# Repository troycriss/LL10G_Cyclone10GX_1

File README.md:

LL10G_Cyclone10GX_1

Test of 10 Gb ethernet output from Cyclone 10 GX dev kit

All switches up (OFF, 1) except S3_2 (and S2_1)
For FMC JTAG not in use, set S5_1 to 0

Quartus Pro 18.1

Program with .sof (via .cdf to open programmer)<br>
Runs for unlimited time, but can't program permanently<br>
See heartbeat LED<br>
Reset Arduino with soft_i2c_cyclone10gx to program SFP outputs (level shifted to 1.8 V)<br>
See red, then green, SFP LEDs<br>
Open system console<br>

 cd hwtesting\\system_console
 
 source main.tcl
 
 SEND 0 10G 80
 
 SENDAGAIN

Set reset pulse duration with (ex: 8) :
 PULSES_pos1dur <duration>

Set write pulse duration with (ex: 7) :
 PULSES_pos2dur <duration>

Set read pulse duration with (ex: 30) :
 PULSES_pos3dur <duration>

https://en.wikipedia.org/wiki/Ethernet_frame <br>
https://en.wikipedia.org/wiki/Internet_Protocol_version_4 <br>
https://en.wikipedia.org/wiki/User_Datagram_Protocol <br>

mac64b_clk; // 156.25 MHz via pll<br>
6.4ns per tick<br>

C10GX kit download: https://www.dropbox.com/s/qehok7muoahcpib/cyclone-10-gx-kit-collateral.zip?dl=0 <br>
  Board test system: https://www.dropbox.com/sh/13s1js1465clt0y/AADcKpqSJ-fH7NIdkqhGLnxYa?dl=0 <br>
  Factory recovery: https://www.dropbox.com/sh/fvxx9ef50a99x4v/AAATVMVC8e21aiI6xPSL01WCa?dl=0 <br>

Simulation of amps: 
https://tinyurl.com/297t5xo8

Simulation of pulse generators:
https://tinyurl.com/27l9ev2u

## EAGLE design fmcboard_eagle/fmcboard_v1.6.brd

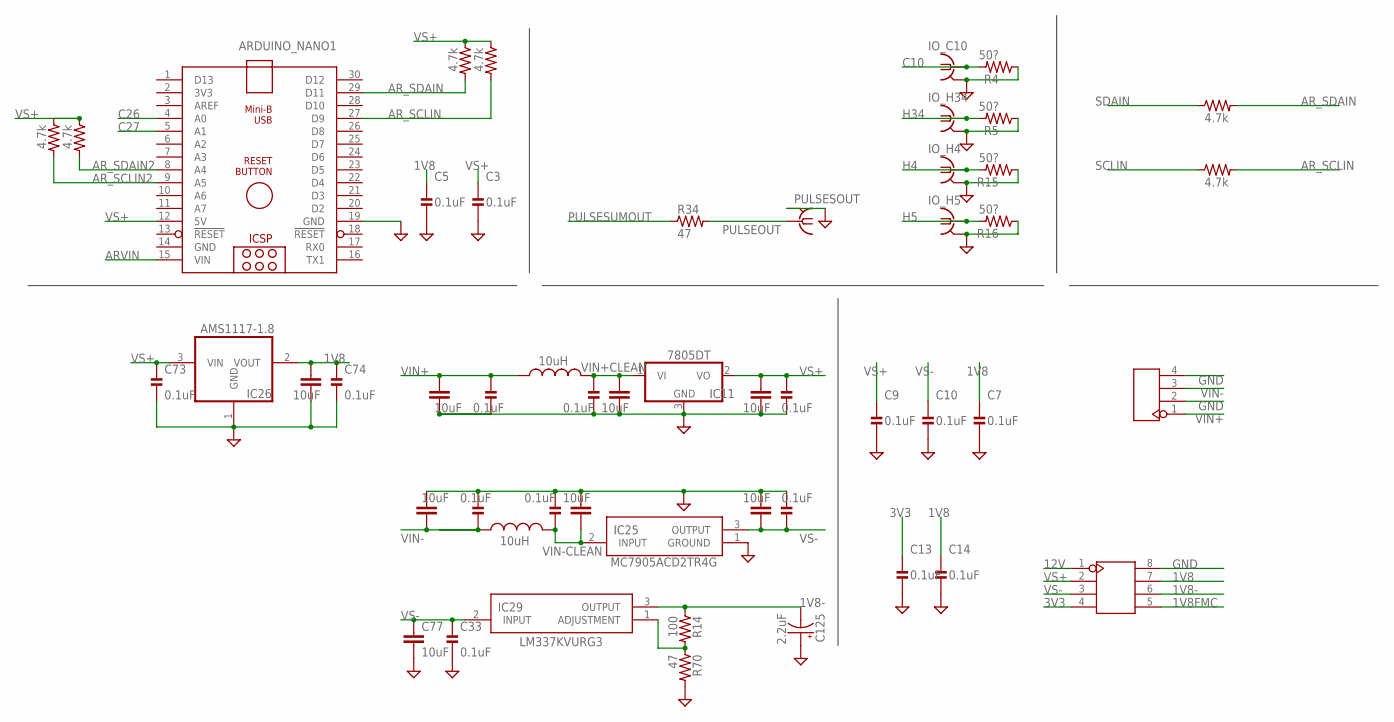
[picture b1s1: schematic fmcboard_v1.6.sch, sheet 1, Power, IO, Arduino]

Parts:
ARDUINO_NANO1: 1; ARDUINO_NANO
C1, C34, C38, C39, C41, C77, C110, C111: 10uF; C0805
C3, C5, C7, C9, C10, C13, C14, C33, C42, C43, C44, C45, C46, C47, C73, C74: 0.1uF; 0402_CAP
C125: 2.2uF; EIA3216; JLC_ROTATION 180
IC11: 7805DT; TO252
IC25: MC7905ACD2TR4G
IC26: AMS1117-1.8; SOT223; JLC_ROTATION 270
IC29: LM337KVURG3
IO_C10: BU-SMB-V
IO_H4, IO_H5, IO_H34: BU-SMB-V
J1: 4p-2.54; H4-2.54
J3: 2X4P-2.54; H2X4-2.54
L1, L2: 10uH; 1210
PULSESOUT: BU-SMB-V
R4, R5, R15, R16: 50?; 0402_RES
R14: 100; 0402_RES
R34, R70: 47; 0402_RES
R48, R49, R50, R51, R87, R90: 4.7k; 0402_RES

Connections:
1V8: C5.1, C7.1, C14.1, C34.1, C74.1, IC26.2 (VOUT), J3.7; also elsewhere on the board
1V8-: C125.C (-), IC29.3 (OUTPUT), J3.6, R14.1; also elsewhere on the board
1V8FMC: J3.5; also elsewhere on the board
3V3: C13.1, J3.4; also elsewhere on the board
12V: J3.1; also elsewhere on the board
ARVIN: ARDUINO_NANO1.15 (VIN)
AR_SCLIN: ARDUINO_NANO1.27 (D9), R51.2, R90.2
AR_SCLIN2: ARDUINO_NANO1.9 (A5), R49.2; also elsewhere on the board
AR_SDAIN: ARDUINO_NANO1.29 (D11), R50.2, R87.2
AR_SDAIN2: ARDUINO_NANO1.8 (A4), R48.2; also elsewhere on the board
C10: IO_C10.1, R4.2; also elsewhere on the board
C26: ARDUINO_NANO1.4 (A0); also elsewhere on the board
C27: ARDUINO_NANO1.5 (A1); also elsewhere on the board
GND: ARDUINO_NANO1.14 (GND), ARDUINO_NANO1.19 (GND), C1.2, C3.2, C5.2, C7.2, C9.2, C10.2, C13.2, C14.2, C33.2, C34.2, C38.2, C39.1, C41.1, C42.2, C43.2, C44.1, C45.1, C46.1, C47.2, C73.2, C74.2, C77.2, C110.2, C111.1, C125.A (+), IC11.3 (GND), IC25.1 (GROUND), IC26.1 (GND), IO_C10.2, IO_C10.3 (2), IO_C10.4 (2), IO_C10.5 (2), IO_H4.2, IO_H4.3 (2), IO_H4.4 (2), IO_H4.5 (2), IO_H5.2, IO_H5.3 (2), IO_H5.4 (2), IO_H5.5 (2), IO_H34.2, IO_H34.3 (2), IO_H34.4 (2), IO_H34.5 (2), J1.2, J1.4, J3.8, PULSESOUT.2, PULSESOUT.3 (2), PULSESOUT.4 (2), PULSESOUT.5 (2), R4.1, R5.1, R15.1, R16.1, R70.2; also elsewhere on the board
H4: IO_H4.1, R15.2; also elsewhere on the board
H5: IO_H5.1, R16.2; also elsewhere on the board
H34: IO_H34.1, R5.2; also elsewhere on the board
unnamed: IC29.1 (ADJUSTMENT), R14.2, R70.1
PULSEOUT: PULSESOUT.1, R34.2; also elsewhere on the board
PULSESUMOUT: R34.1; also elsewhere on the board
SCLIN: R90.1; also elsewhere on the board
SDAIN: R87.1; also elsewhere on the board
VIN+: C1.1, C42.1, J1.1, L1.1; also elsewhere on the board
VIN+CLEAN: C43.1, C110.1, IC11.1 (VI), L1.2
VIN-: C41.2, C44.2, J1.3, L2.1; also elsewhere on the board
VIN-CLEAN: C45.2, C111.2, IC25.2 (INPUT), L2.2
VS+: ARDUINO_NANO1.12 (5V), C3.1, C9.1, C38.1, C47.1, C73.1, IC11.2 (VO), IC26.3 (VIN), J3.2, R48.1, R49.1, R50.1, R51.1; also elsewhere on the board
VS-: C10.1, C33.1, C39.2, C46.2, C77.1, IC25.3 (OUTPUT), IC29.2 (INPUT), J3.3; also elsewhere on the board

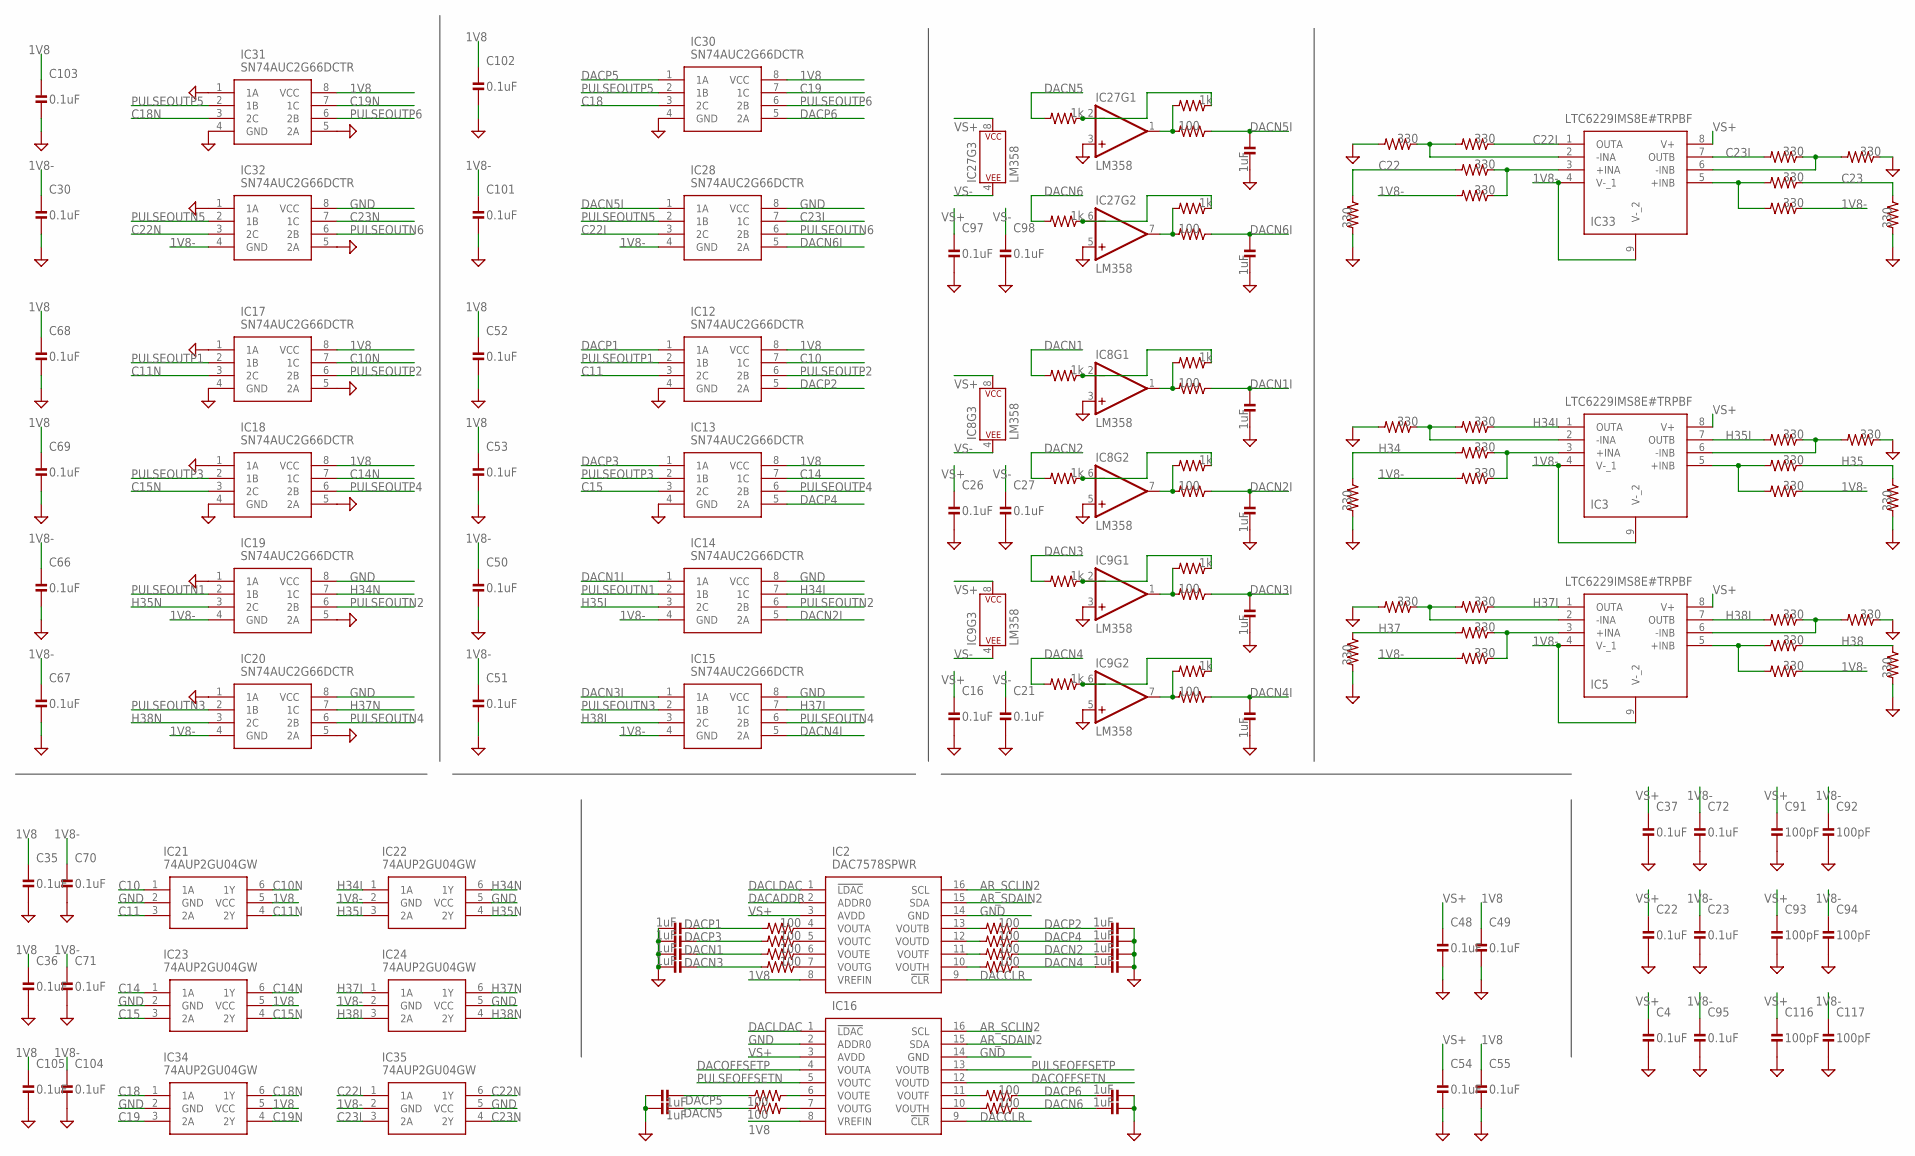
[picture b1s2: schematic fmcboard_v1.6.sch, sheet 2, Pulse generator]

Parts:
C4, C16, C21, C22, C23, C26, C27, C30, C35, C36, C37, C48, C49, C50, C51, C52, C53, C54, C55, C66, C67, C68, C69, C70, C71, C72, C95, C97, C98, C101, C102, C103, C104, C105: 0.1uF; 0402_CAP
C17, C18, C19, C20, C31, C56, C57, C58, C59, C60, C61, C62, C63, C89, C90, C96, C99, C100: 1uF; 0402_CAP
C91, C92, C93, C94, C116, C117: 100pF; 0402_CAP
IC2, IC16: DAC7578SPWR; SOP65P640X120-16N
IC3, IC5, IC33: LTC6229IMS8E#TRPBF; SOP65P490X110-9N
IC8, IC9, IC27: LM358; SO08
IC12, IC13, IC14, IC15, IC17, IC18, IC19, IC20, IC28, IC30, IC31, IC32: SN74AUC2G66DCTR; SOP65P400X130-8N
IC21, IC22, IC23, IC24, IC34, IC35: 74AUP2GU04GW; SOT65P210X110-6N
R21, R22, R23, R24, R27, R28, R29, R30, R37, R39, R41, R43, R44, R45, R46, R52, R80, R81, R82, R83, R91, R102, R103, R104, R105, R106, R107, R108, R109, R110: 330; 0402_RES
R47, R53, R54, R55, R56, R57, R58, R59, R74, R75, R76, R77, R92, R93, R94, R95, R100, R101: 100; 0402_RES
R62, R63, R64, R65, R66, R67, R68, R69, R96, R97, R98, R99: 1k; 0402_RES

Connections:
1V8: C35.1, C36.1, C49.1, C52.1, C53.1, C55.1, C68.1, C69.1, C102.1, C103.1, C105.1, IC2.8 (VREFIN), IC12.8 (VCC), IC13.8 (VCC), IC16.8 (VREFIN), IC17.8 (VCC), IC18.8 (VCC), IC21.5 (VCC), IC23.5 (VCC), IC30.8 (VCC), IC31.8 (VCC), IC34.5 (VCC); also elsewhere on the board
1V8-: C23.1, C30.1, C50.1, C51.1, C66.1, C67.1, C70.1, C71.1, C72.1, C92.1, C94.1, C95.1, C101.1, C104.1, C117.1, IC3.4 (V-_1), IC3.9 (V-_2), IC5.4 (V-_1), IC5.9 (V-_2), IC14.4 (GND), IC15.4 (GND), IC19.4 (GND), IC20.4 (GND), IC22.2 (GND), IC24.2 (GND), IC28.4 (GND), IC32.4 (GND), IC33.4 (V-_1), IC33.9 (V-_2), IC35.2 (GND), R22.2, R28.1, R39.2, R45.1, R102.2, R106.1; also elsewhere on the board
AR_SCLIN2: IC2.16 (SCL), IC16.16 (SCL); also elsewhere on the board
AR_SDAIN2: IC2.15 (SDA), IC16.15 (SDA); also elsewhere on the board
C10: IC12.7 (1C), IC21.1 (1A); also elsewhere on the board
C10N: IC17.7 (1C), IC21.6 (1Y)
C11: IC12.3 (2C), IC21.3 (2A); also elsewhere on the board
C11N: IC17.3 (2C), IC21.4 (2Y)
C14: IC13.7 (1C), IC23.1 (1A); also elsewhere on the board
C14N: IC18.7 (1C), IC23.6 (1Y)
C15: IC13.3 (2C), IC23.3 (2A); also elsewhere on the board
C15N: IC18.3 (2C), IC23.4 (2Y)
C18: IC30.3 (2C), IC34.1 (1A); also elsewhere on the board
C18N: IC31.3 (2C), IC34.6 (1Y)
C19: IC30.7 (1C), IC34.3 (2A); also elsewhere on the board
C19N: IC31.7 (1C), IC34.4 (2Y)
C22: R91.2, R109.1; also elsewhere on the board
C22I: IC28.3 (2C), IC33.1 (OUTA), IC35.1 (1A), R103.1
C22N: IC32.3 (2C), IC35.6 (1Y)
C23: R105.1, R110.1; also elsewhere on the board
C23I: IC28.7 (1C), IC33.7 (OUTB), IC35.3 (2A), R107.2
C23N: IC32.7 (1C), IC35.4 (2Y)
DACADDR: IC2.2 (ADDR0)
DACCLR: IC2.9 (!CLR), IC16.9 (!CLR)
DACLDAC: IC2.1 (!LDAC), IC16.1 (!LDAC)
DACN1: C57.2, R54.2, R64.2
DACN1I: C17.2, IC14.1 (1A), R74.1
DACN2: C61.1, R58.1, R65.2
DACN2I: C18.2, IC14.5 (2A), R75.1
DACN3: C56.2, R55.2, R68.2
DACN3I: C19.2, IC15.1 (1A), R76.1
DACN4: C60.1, R59.1, R69.2
DACN4I: C20.2, IC15.5 (2A), R77.1
DACN5: C96.1, R95.1, R98.2
DACN5I: C99.2, IC28.1 (1A), R100.1
DACN6: C89.1, R93.1, R99.2
DACN6I: C100.2, IC28.5 (2A), R101.1
DACOFFSETN: IC16.12 (VOUTD); also elsewhere on the board
DACOFFSETP: IC16.4 (VOUTA); also elsewhere on the board
DACP1: C59.2, IC12.1 (1A), R47.2
DACP2: C63.1, IC12.5 (2A), R56.1
DACP3: C58.2, IC13.1 (1A), R53.2
DACP4: C62.1, IC13.5 (2A), R57.1
DACP5: C90.1, IC30.1 (1A), R94.1
DACP6: C31.1, IC30.5 (2A), R92.1
GND: C4.2, C16.2, C17.1, C18.1, C19.1, C20.1, C21.2, C22.2, C23.2, C26.2, C27.2, C30.2, C31.2, C35.2, C36.2, C37.2, C48.2, C49.2, C50.2, C51.2, C52.2, C53.2, C54.2, C55.2, C56.1, C57.1, C58.1, C59.1, C60.2, C61.2, C62.2, C63.2, C66.2, C67.2, C68.2, C69.2, C70.2, C71.2, C72.2, C89.2, C90.2, C91.2, C92.2, C93.2, C94.2, C95.2, C96.2, C97.2, C98.2, C99.1, C100.1, C101.2, C102.2, C103.2, C104.2, C105.2, C116.2, C117.2, IC2.14 (GND), IC8.3 (+IN), IC8.5 (+IN), IC9.3 (+IN), IC9.5 (+IN), IC12.4 (GND), IC13.4 (GND), IC14.8 (VCC), IC15.8 (VCC), IC16.2 (ADDR0), IC16.14 (GND), IC17.1 (1A), IC17.4 (GND), IC17.5 (2A), IC18.1 (1A), IC18.4 (GND), IC18.5 (2A), IC19.1 (1A), IC19.5 (2A), IC19.8 (VCC), IC20.1 (1A), IC20.5 (2A), IC20.8 (VCC), IC21.2 (GND), IC22.5 (VCC), IC23.2 (GND), IC24.5 (VCC), IC27.3 (+IN), IC27.5 (+IN), IC28.8 (VCC), IC30.4 (GND), IC31.1 (1A), IC31.4 (GND), IC31.5 (2A), IC32.1 (1A), IC32.5 (2A), IC32.8 (VCC), IC34.2 (GND), IC35.5 (VCC), R24.2, R30.1, R43.2, R52.1, R80.2, R81.2, R82.2, R83.2, R104.2, R108.1, R109.2, R110.2; also elsewhere on the board
H34: R21.2, R80.1; also elsewhere on the board
H34I: IC3.1 (OUTA), IC14.7 (1C), IC22.1 (1A), R23.1
H34N: IC19.7 (1C), IC22.6 (1Y)
H35: R27.1, R81.1; also elsewhere on the board
H35I: IC3.7 (OUTB), IC14.3 (2C), IC22.3 (2A), R29.2
H35N: IC19.3 (2C), IC22.4 (2Y)
H37: R37.2, R83.1; also elsewhere on the board
H37I: IC5.1 (OUTA), IC15.7 (1C), IC24.1 (1A), R41.1
H37N: IC20.7 (1C), IC24.6 (1Y)
H38: R44.1, R82.1; also elsewhere on the board
H38I: IC5.7 (OUTB), IC15.3 (2C), IC24.3 (2A), R46.2
H38N: IC20.3 (2C), IC24.4 (2Y)
unnamed: IC33.2 (-INA), R103.2, R104.1
unnamed: IC3.6 (-INB), R29.1, R30.2
unnamed: IC3.5 (+INB), R27.2, R28.2
unnamed: IC5.2 (-INA), R41.2, R43.1
unnamed: IC3.3 (+INA), R21.1, R22.1
unnamed: IC5.6 (-INB), R46.1, R52.2
unnamed: IC3.2 (-INA), R23.2, R24.1
unnamed: IC5.3 (+INA), R37.1, R39.1
unnamed: IC5.5 (+INB), R44.2, R45.2
unnamed: IC8.7 (OUT), R62.2, R75.2
unnamed: IC8.1 (OUT), R63.2, R74.2
unnamed: IC16.11 (VOUTF), R92.2
unnamed: IC8.2 (-IN), R63.1, R64.1
unnamed: IC8.6 (-IN), R62.1, R65.1
unnamed: IC2.13 (VOUTB), R56.2
unnamed: IC2.4 (VOUTA), R47.1
unnamed: IC2.5 (VOUTC), R53.1
unnamed: IC2.6 (VOUTE), R54.1
unnamed: IC2.7 (VOUTG), R55.1
unnamed: IC2.12 (VOUTD), R57.2
unnamed: IC2.11 (VOUTF), R58.2
unnamed: IC2.10 (VOUTH), R59.2
unnamed: IC9.7 (OUT), R66.2, R77.2
unnamed: IC9.1 (OUT), R67.2, R76.2
unnamed: IC9.2 (-IN), R67.1, R68.1
unnamed: IC9.6 (-IN), R66.1, R69.1
unnamed: IC16.10 (VOUTH), R93.2
unnamed: IC16.6 (VOUTE), R94.2
unnamed: IC16.7 (VOUTG), R95.2
unnamed: IC27.7 (OUT), R96.2, R101.2
unnamed: IC27.1 (OUT), R97.2, R100.2
unnamed: IC27.2 (-IN), R97.1, R98.1
unnamed: IC27.6 (-IN), R96.1, R99.1
unnamed: IC33.6 (-INB), R107.1, R108.2
unnamed: IC33.3 (+INA), R91.1, R102.1
unnamed: IC33.5 (+INB), R105.2, R106.2
PULSEOFFSETN: IC16.5 (VOUTC); also elsewhere on the board
PULSEOFFSETP: IC16.13 (VOUTB); also elsewhere on the board
PULSEOUTN1: IC14.2 (1B), IC19.2 (1B); also elsewhere on the board
PULSEOUTN2: IC14.6 (2B), IC19.6 (2B); also elsewhere on the board
PULSEOUTN3: IC15.2 (1B), IC20.2 (1B); also elsewhere on the board
PULSEOUTN4: IC15.6 (2B), IC20.6 (2B); also elsewhere on the board
PULSEOUTN5: IC28.2 (1B), IC32.2 (1B); also elsewhere on the board
PULSEOUTN6: IC28.6 (2B), IC32.6 (2B); also elsewhere on the board
PULSEOUTP1: IC12.2 (1B), IC17.2 (1B); also elsewhere on the board
PULSEOUTP2: IC12.6 (2B), IC17.6 (2B); also elsewhere on the board
PULSEOUTP3: IC13.2 (1B), IC18.2 (1B); also elsewhere on the board
PULSEOUTP4: IC13.6 (2B), IC18.6 (2B); also elsewhere on the board
PULSEOUTP5: IC30.2 (1B), IC31.2 (1B); also elsewhere on the board
PULSEOUTP6: IC30.6 (2B), IC31.6 (2B); also elsewhere on the board
VS+: C4.1, C16.1, C22.1, C26.1, C37.1, C48.1, C54.1, C91.1, C93.1, C97.1, C116.1, IC2.3 (AVDD), IC3.8 (V+), IC5.8 (V+), IC8.8 (P$V+), IC9.8 (P$V+), IC16.3 (AVDD), IC27.8 (P$V+), IC33.8 (V+); also elsewhere on the board
VS-: C21.1, C27.1, C98.1, IC8.4 (P$V-), IC9.4 (P$V-), IC27.4 (P$V-); also elsewhere on the board

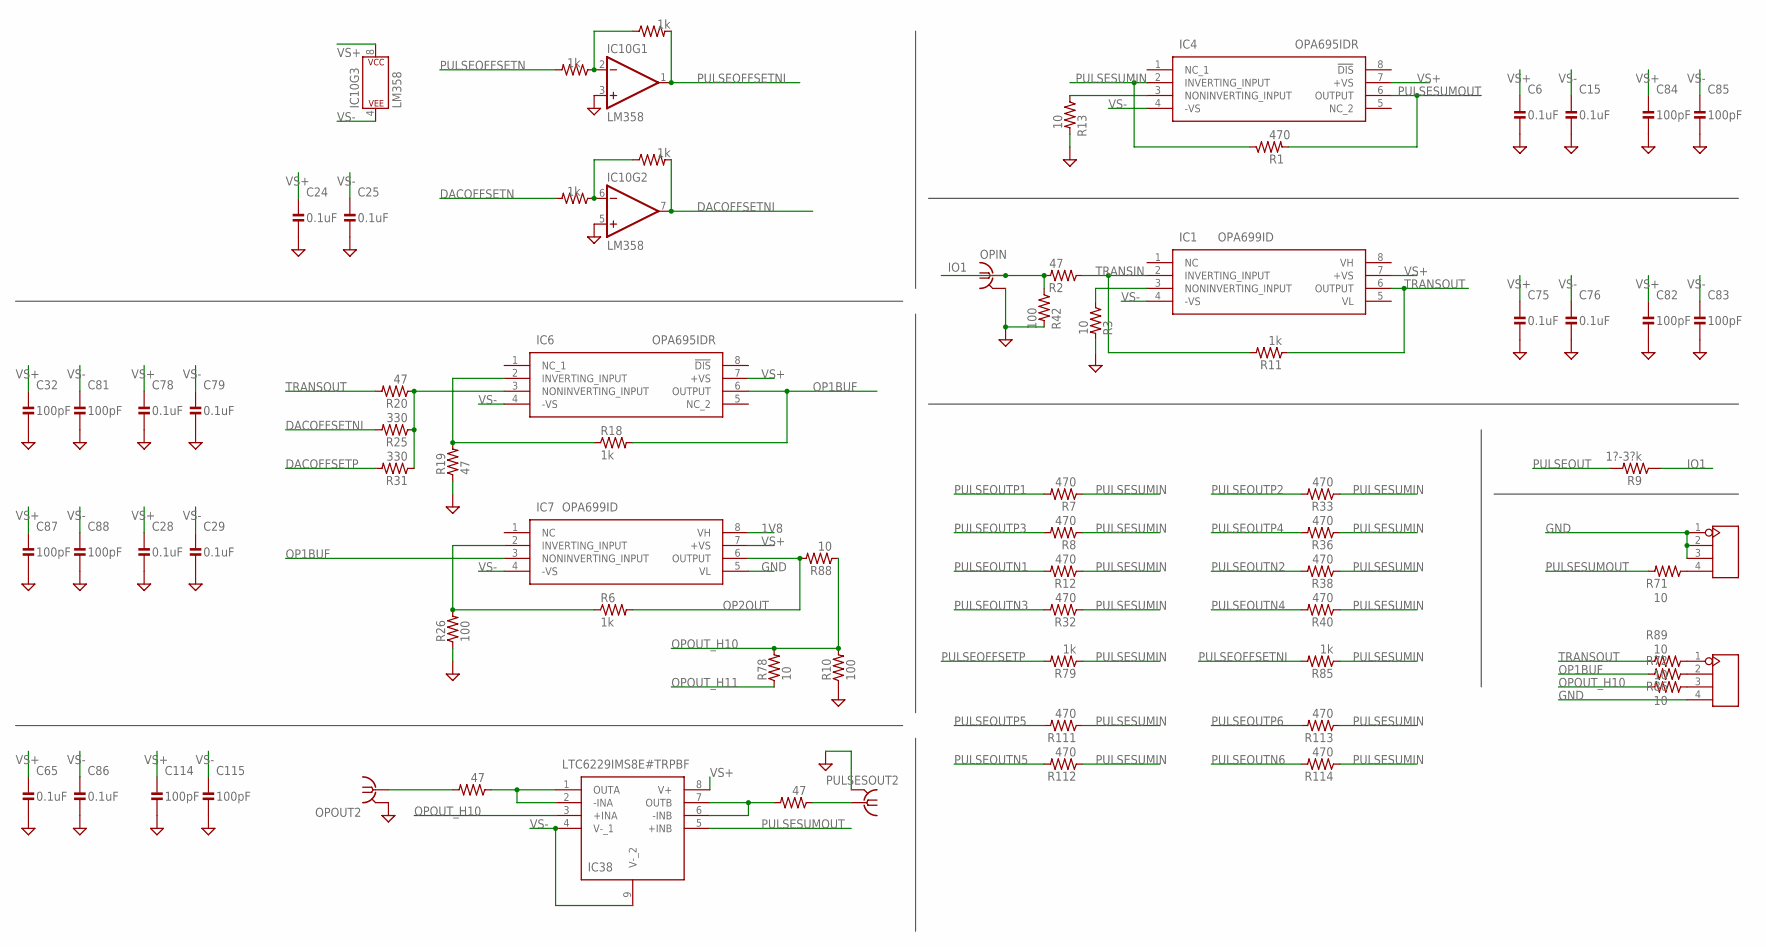
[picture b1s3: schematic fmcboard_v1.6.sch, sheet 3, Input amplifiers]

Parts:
C6, C15, C24, C25, C28, C29, C65, C75, C76, C78, C79, C86: 0.1uF; 0402_CAP
C32, C81, C82, C83, C84, C85, C87, C88, C114, C115: 100pF; 0402_CAP
IC1, IC7: OPA699ID; SOIC127P600X175-8N
IC4, IC6: OPA695IDR; SOIC127P600X175-8N
IC10: LM358; SO08
IC38: LTC6229IMS8E#TRPBF; SOP65P490X110-9N
J5, J13: 4p-2.54; H4-2.54
OPIN: BU-SMB-V
OPOUT2: BU-SMB-V
PULSESOUT2: BU-SMB-V
R1, R7, R8, R12, R32, R33, R36, R38, R40, R111, R112, R113, R114: 470; 0402_RES
R2, R19, R20, R119, R120: 47; 0402_RES
R3, R13, R71, R72, R78, R86, R88, R89: 10; 0402_RES
R6, R11, R17, R18, R35, R61, R79, R85, R115: 1k; 0402_RES
R9: 1?-3?k; R0805
R10, R26, R42: 100; 0402_RES
R25, R31: 330; 0402_RES

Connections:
1V8: IC7.8 (VH); also elsewhere on the board
DACOFFSETN: R17.2; also elsewhere on the board
DACOFFSETNI: IC10.7 (OUT), R25.2, R115.2
DACOFFSETP: R31.2; also elsewhere on the board
GND: C6.2, C15.2, C24.2, C25.2, C28.2, C29.2, C32.2, C65.2, C75.2, C76.2, C78.2, C79.2, C81.2, C82.2, C83.2, C84.2, C85.2, C86.2, C87.2, C88.2, C114.2, C115.2, IC7.5 (VL), IC10.3 (+IN), IC10.5 (+IN), J5.4, J13.1, J13.2, J13.3, OPIN.2, OPIN.3 (2), OPIN.4 (2), OPIN.5 (2), OPOUT2.2, OPOUT2.3 (2), OPOUT2.4 (2), OPOUT2.5 (2), PULSESOUT2.2, PULSESOUT2.3 (2), PULSESOUT2.4 (2), PULSESOUT2.5 (2), R3.2, R10.1, R13.2, R19.1, R26.1, R42.2; also elsewhere on the board
IO1: OPIN.1, R2.2, R9.1, R42.1
unnamed: IC10.6 (-IN), R17.1, R115.1
unnamed: IC1.3 (NONINVERTING_INPUT), R3.1
unnamed: IC4.3 (NONINVERTING_INPUT), R13.1
unnamed: IC6.2 (INVERTING_INPUT), R18.1, R19.2
unnamed: IC6.3 (NONINVERTING_INPUT), R20.1, R25.1, R31.1
unnamed: IC7.2 (INVERTING_INPUT), R6.1, R26.2
unnamed: IC38.1 (OUTA), IC38.2 (-INA), R119.1
unnamed: J5.2, R72.1
unnamed: IC10.2 (-IN), R35.1, R61.1
unnamed: PULSESOUT2.1, R120.1
unnamed: J5.3, R86.1
unnamed: J5.1, R89.1
unnamed: OPOUT2.1, R119.2
unnamed: J13.4, R71.1
unnamed: IC38.6 (-INB), IC38.7 (OUTB), R120.2
OP1BUF: IC6.6 (OUTPUT), IC7.3 (NONINVERTING_INPUT), R18.2, R72.2
OP2OUT: IC7.6 (OUTPUT), R6.2, R88.2
OPOUT_H10: IC38.3 (+INA), R10.2, R78.2, R86.2, R88.1; also elsewhere on the board
OPOUT_H11: R78.1; also elsewhere on the board
PULSEOFFSETN: R61.2; also elsewhere on the board
PULSEOFFSETNI: IC10.1 (OUT), R35.2, R85.2
PULSEOFFSETP: R79.2; also elsewhere on the board
PULSEOUT: R9.2; also elsewhere on the board
PULSEOUTN1: R12.2; also elsewhere on the board
PULSEOUTN2: R38.2; also elsewhere on the board
PULSEOUTN3: R32.2; also elsewhere on the board
PULSEOUTN4: R40.2; also elsewhere on the board
PULSEOUTN5: R112.2; also elsewhere on the board
PULSEOUTN6: R114.2; also elsewhere on the board
PULSEOUTP1: R7.2; also elsewhere on the board
PULSEOUTP2: R33.2; also elsewhere on the board
PULSEOUTP3: R8.2; also elsewhere on the board
PULSEOUTP4: R36.2; also elsewhere on the board
PULSEOUTP5: R111.2; also elsewhere on the board
PULSEOUTP6: R113.2; also elsewhere on the board
PULSESUMIN: IC4.2 (INVERTING_INPUT), R1.1, R7.1, R8.1, R12.1, R32.1, R33.1, R36.1, R38.1, R40.1, R79.1, R85.1, R111.1, R112.1, R113.1, R114.1
PULSESUMOUT: IC4.6 (OUTPUT), IC38.5 (+INB), R1.2, R71.2; also elsewhere on the board
TRANSIN: IC1.2 (INVERTING_INPUT), R2.1, R11.2
TRANSOUT: IC1.6 (OUTPUT), R11.1, R20.2, R89.2
VS+: C6.1, C24.1, C28.1, C32.1, C65.1, C75.1, C78.1, C82.1, C84.1, C87.1, C114.1, IC1.7 (+VS), IC4.7 (+VS), IC6.7 (+VS), IC7.7 (+VS), IC10.8 (P$V+), IC38.8 (V+); also elsewhere on the board
VS-: C15.1, C25.1, C29.1, C76.1, C79.1, C81.1, C83.1, C85.1, C86.1, C88.1, C115.1, IC1.4 (-VS), IC4.4 (-VS), IC6.4 (-VS), IC7.4 (-VS), IC10.4 (P$V-), IC38.4 (V-_1), IC38.9 (V-_2); also elsewhere on the board

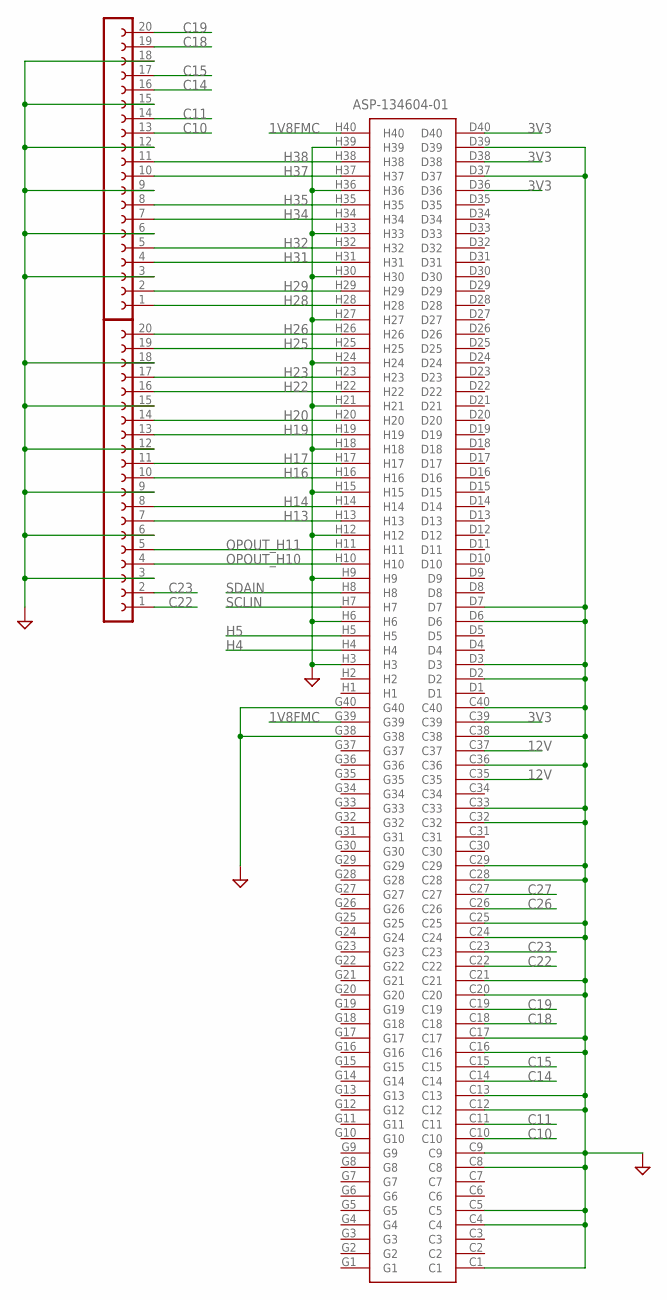
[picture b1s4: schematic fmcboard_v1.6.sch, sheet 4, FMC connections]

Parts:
J2: ASP-134604-01; ASP13460401
SV1, SV2: 20; FE20

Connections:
1V8FMC: J2.G39, J2.H40; also elsewhere on the board
3V3: J2.C39, J2.D36, J2.D38, J2.D40; also elsewhere on the board
12V: J2.C35, J2.C37; also elsewhere on the board
C10: J2.C10, SV2.13; also elsewhere on the board
C11: J2.C11, SV2.14; also elsewhere on the board
C14: J2.C14, SV2.16; also elsewhere on the board
C15: J2.C15, SV2.17; also elsewhere on the board
C18: J2.C18, SV2.19; also elsewhere on the board
C19: J2.C19, SV2.20; also elsewhere on the board
C22: J2.C22, SV1.1; also elsewhere on the board
C23: J2.C23, SV1.2; also elsewhere on the board
C26: J2.C26; also elsewhere on the board
C27: J2.C27; also elsewhere on the board
GND: J2.C1, J2.C4, J2.C5, J2.C8, J2.C9, J2.C12, J2.C13, J2.C16, J2.C17, J2.C20, J2.C21, J2.C24, J2.C25, J2.C28, J2.C29, J2.C32, J2.C33, J2.C36, J2.C38, J2.C40, J2.D2, J2.D3, J2.D6, J2.D7, J2.D37, J2.D39, J2.G38, J2.G40, J2.H3, J2.H6, J2.H9, J2.H12, J2.H15, J2.H18, J2.H21, J2.H24, J2.H27, J2.H30, J2.H33, J2.H36, J2.H39, SV1.3, SV1.6, SV1.9, SV1.12, SV1.15, SV1.18, SV2.3, SV2.6, SV2.9, SV2.12, SV2.15, SV2.18; also elsewhere on the board
H4: J2.H4; also elsewhere on the board
H5: J2.H5; also elsewhere on the board
H13: J2.H13, SV1.7
H14: J2.H14, SV1.8
H16: J2.H16, SV1.10
H17: J2.H17, SV1.11
H19: J2.H19, SV1.13
H20: J2.H20, SV1.14
H22: J2.H22, SV1.16
H23: J2.H23, SV1.17
H25: J2.H25, SV1.19
H26: J2.H26, SV1.20
H28: J2.H28, SV2.1
H29: J2.H29, SV2.2
H31: J2.H31, SV2.4
H32: J2.H32, SV2.5
H34: J2.H34, SV2.7; also elsewhere on the board
H35: J2.H35, SV2.8; also elsewhere on the board
H37: J2.H37, SV2.10; also elsewhere on the board
H38: J2.H38, SV2.11; also elsewhere on the board
OPOUT_H10: J2.H10, SV1.4; also elsewhere on the board
OPOUT_H11: J2.H11, SV1.5; also elsewhere on the board
SCLIN: J2.H7; also elsewhere on the board
SDAIN: J2.H8; also elsewhere on the board

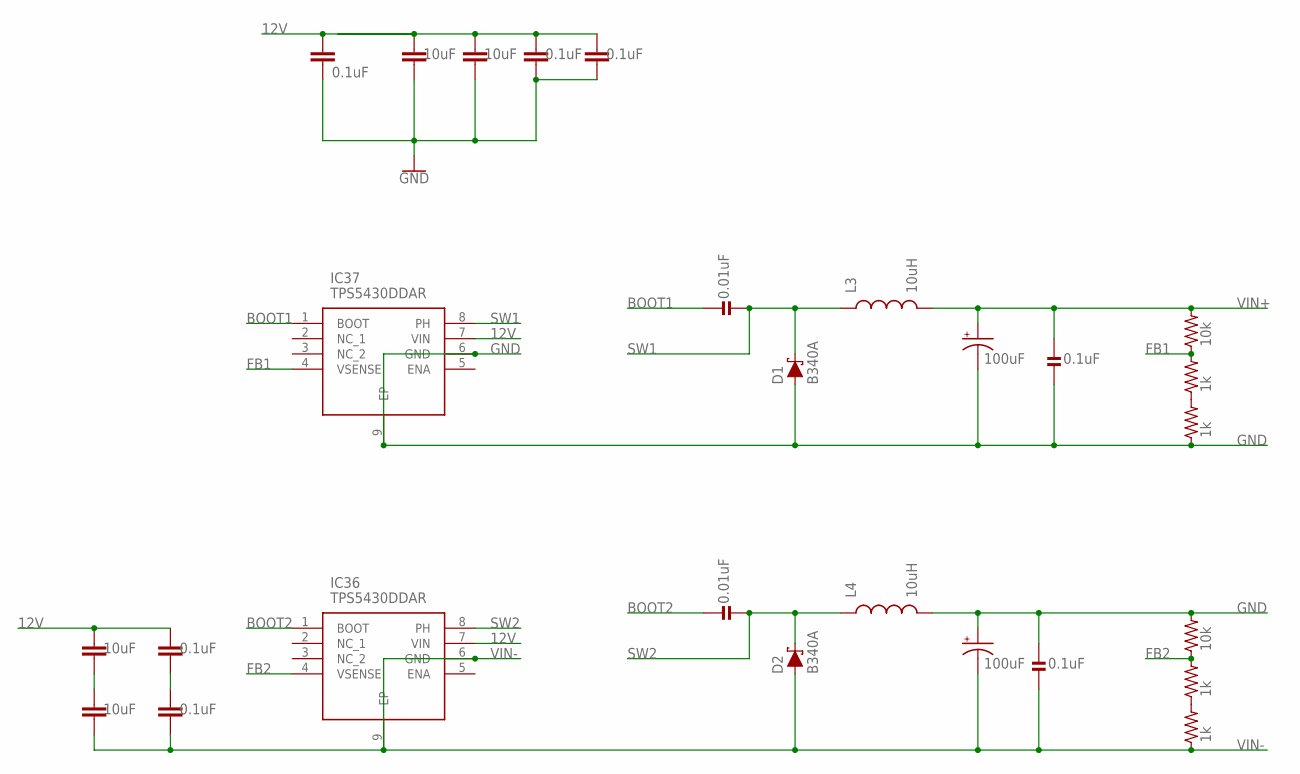
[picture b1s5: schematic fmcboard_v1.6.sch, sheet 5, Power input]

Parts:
C2, C40: 100uF; VISHAY_C; LCSC C7230
C8, C11, C12, C108, C113: 0.1uF; C0805K
C64, C80, C109, C112: 10uF; C0805
C106, C121: 0.1uF; 0402_CAP
C107, C122: 0.01uF; 0402_CAP
D1, D2: B340A; SMA-DIODE; LCSC C64982
IC36, IC37: TPS5430DDAR; SOIC127P600X170-9N
L3, L4: 10uH; CDRH125; LCSC C339970
R60, R84, R116, R117: 1k; 0402_RES
R73, R118: 10k; 0402_RES

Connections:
12V: C8.1, C11.1, C12.1, C64.1, C80.1, C108.1, C112.1, IC36.7 (VIN), IC37.7 (VIN); also elsewhere on the board
BOOT1: C122.1, IC37.1 (BOOT)
BOOT2: C107.1, IC36.1 (BOOT)
FB1: IC37.4 (VSENSE), R60.2, R73.1
FB2: IC36.4 (VSENSE), R116.2, R118.1
GND: C2.-, C8.2, C11.2, C12.2, C40.+, C64.2, C80.2, C106.1, C121.2, D1.A, IC37.6 (GND), IC37.9 (EP), L4.2, R84.1, R118.2; also elsewhere on the board
unnamed: C108.2, C113.1
unnamed: C109.1, C112.2
unnamed: R60.1, R84.2
unnamed: R116.1, R117.2
SW1: C122.2, D1.C, IC37.8 (PH), L3.1
SW2: C107.2, D2.C, IC36.8 (PH), L4.1
VIN+: C2.+, C121.1, L3.2, R73.2; also elsewhere on the board
VIN-: C40.-, C106.2, C109.2, C113.2, D2.A, IC36.6 (GND), IC36.9 (EP), R117.1; also elsewhere on the board

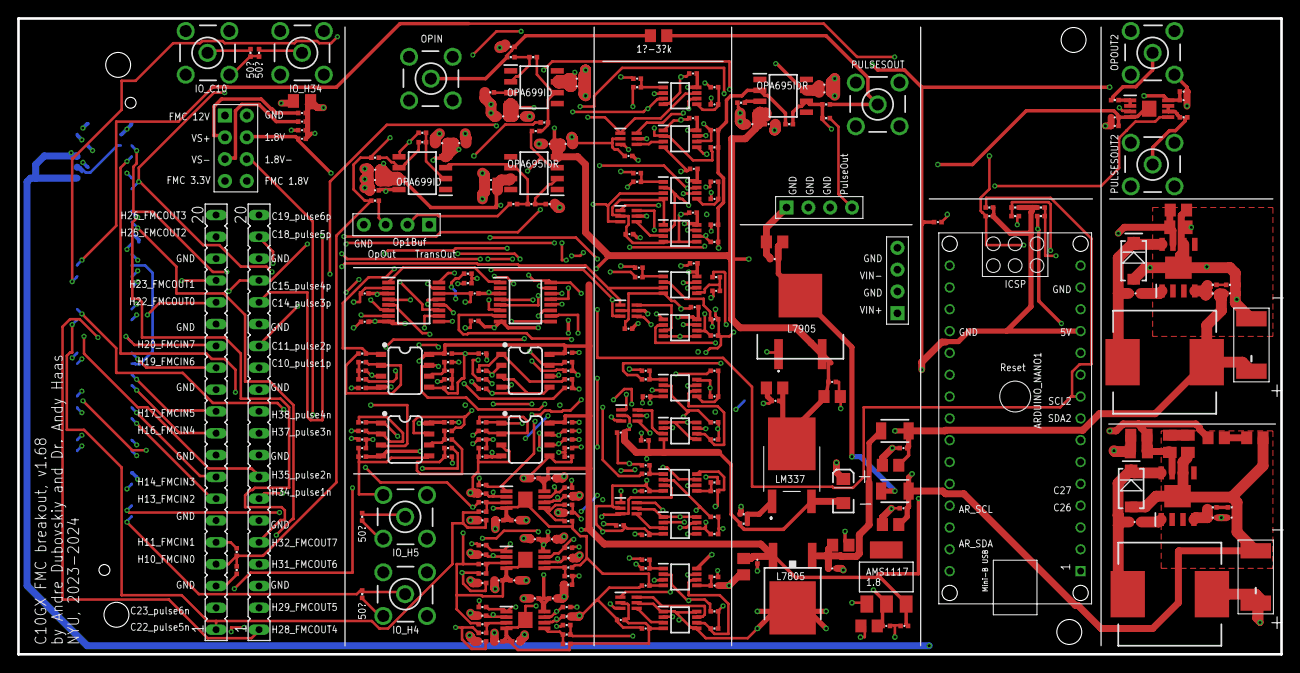
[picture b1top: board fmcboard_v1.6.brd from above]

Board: 4 copper layers, 147.0 x 74.0 mm, 300 parts (1 on the bottom side), 176 nets.

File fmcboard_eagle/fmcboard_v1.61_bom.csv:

Comment,Designator,Footprint,LCSC Part #
0.1uF,C3 C4 C5 C6 C7 C8 C9 C10 C12 C13 C14 C15 C16 C21 C22 C23 C24 C25 C26 C27 C28 C29 C30 C31 C35 C36 C37 C42 C43 C44 C45 C46 C47 C48 C49 C50 C51 C52 C53 C54 C55 C66 C67 C68 C69 C70 C71 C72 C73 C74 C75 C76 C78 C79,0805,
1,ARDUINO_NANO1,ARDUINO_NANO,
1k,R20 R62 R63 R64 R65 R66 R67 R68 R69 R71 R72,R0805,
1uF,C17 C18 C19 C20 C56 C57 C58 C59 C60 C61 C62 C63 C64 C77,0805,
4.7k,R25 R31 R48 R49 R50 R51,R0805,
4p-2.54,J3 J4 J6 J7 J8 J12,H4-2.54,
5k,R_O2 R_VH R_VL,RTRIM3296W,
8pin,J1 J5 J9,1X08,
10k,R42 R80 R81 R82 R83,R0805,
10uF,C1 C2 C34 C38 C39 C40 C41,0805,
10uH,L1 L2,1210,C1882517
20,SV1 SV2,FE20,
47,R2 R19 R34,R0805,
50,R4 R5 R15 R16,AXIAL-0.3,
74AUP2GU04GW,IC21 IC22 IC23 IC24,SOT65P210X110-6N,
100,R3 R10 R13 R26 R47 R53 R54 R55 R56 R57 R58 R59 R60 R74 R75 R76 R77 R78,R0805,
100k,R17,R0805,
330,R1 R7 R8 R12 R18 R21 R22 R23 R24 R27 R28 R29 R30 R32 R33 R36 R37 R38 R39 R40 R41 R43 R44 R45 R46 R52,R0805,
470,R6 R9 R11,R0805,
7805TV,IC11,TO220V,
AMS1117-1.8,IC26,SOT223,
ASP-134604-01,J2,ASP13460401,
BU-SMB-V,IO_C10 IO_H4 IO_H5 IO_H34 OPIN PULSESUMOUT,BU-SMB-V,
DAC7578SPWR,IC2 IC16,SOP65P640X120-16N,
LM358,IC8 IC9 IC10,SO08,
LTC6229IMS8E#TRPBF,IC3 IC5,SOP65P490X110-9N,
OPA695IDR,IC1 IC4 IC6,SOIC127P600X175-8N,
OPA699ID,IC7 IC27,SOIC127P600X175-8N,
SN74AUC2G66DCTR,IC12 IC13 IC14 IC15 IC17 IC18 IC19 IC20,SOP65P400X130-8N,
STMICROELECTRONICS_L7905ACVSTMICROELECTRONICS_L7905ACV_0_0,U2,STMICROELECTRONICS_L7905ACV_0,
TXS0108EPWR,U1,TSSOP20-0.65-6.5X4.4MM,

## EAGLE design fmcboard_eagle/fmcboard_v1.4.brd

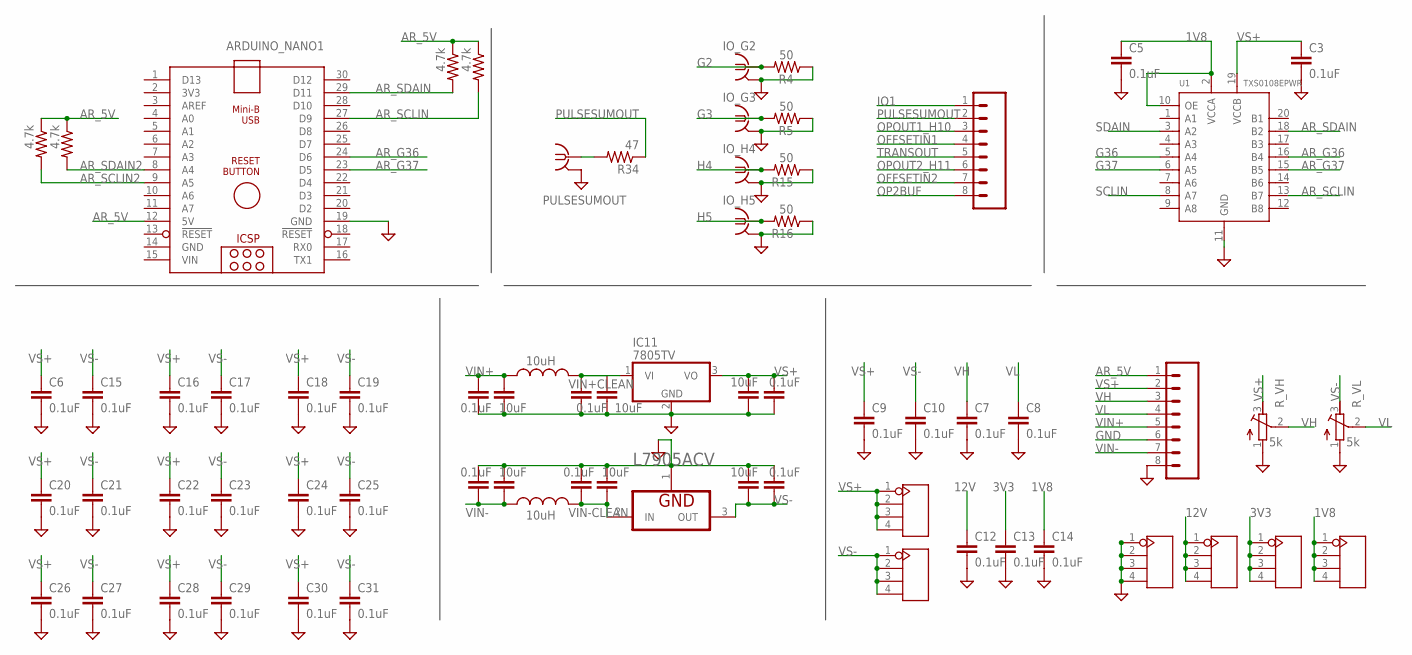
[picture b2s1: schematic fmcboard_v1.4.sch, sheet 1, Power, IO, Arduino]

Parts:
ARDUINO_NANO1: 1; ARDUINO_NANO
C1, C2, C38, C39, C40, C41: 10uF; CAP-PTH-5MM
C3, C5, C6, C7, C8, C9, C10, C12, C13, C14, C15, C16, C17, C18, C19, C20, C21, C22, C23, C24, C25, C26, C27, C28, C29, C30, C31, C42, C43, C44, C45, C46, C47: 0.1uF; 0805
IC11: 7805TV; TO220V
IO_G2, IO_G3: BU-SMB-V
IO_H4, IO_H5: BU-SMB-V
J1, J5: 8pin; 1X08
J3, J4, J6, J7, J8, J12: 4p-2.54; H4-2.54
L1, L2: 10uH; 6000-XXXX-RC
PULSESUMOUT: BU-SMB-V
R4, R5, R15, R16: 50; AXIAL-0.3
R34: 47; R0805
R48, R49, R50, R51: 4.7k; R0805
R_VH: 5k; RTRIM3296W
R_VL: 5k; RTRIM3296W
U1: TXS0108EPWR; TSSOP20-0.65-6.5X4.4MM
U2: STMICROELECTRONICS_L7905ACVSTMICROELECTRONICS_L79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; STMICROELECTRONICS_L7905ACV_0

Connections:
1V8: C5.1, C14.1, J12.1, J12.2, J12.3, J12.4, U1.2 (VCCA), U1.10 (OE); also elsewhere on the board
3V3: C13.1, J3.1, J3.2, J3.3, J3.4; also elsewhere on the board
12V: C12.1, J8.1, J8.2, J8.3, J8.4; also elsewhere on the board
AR_5V: ARDUINO_NANO1.12 (5V), J1.1, R48.1, R49.1, R50.1, R51.1
AR_G36: ARDUINO_NANO1.24 (D6), U1.16 (B4)
AR_G37: ARDUINO_NANO1.23 (D5), U1.15 (B5)
AR_SCLIN: ARDUINO_NANO1.27 (D9), R51.2, U1.13 (B7)
AR_SCLIN2: ARDUINO_NANO1.9 (A5), R49.2; also elsewhere on the board
AR_SDAIN: ARDUINO_NANO1.29 (D11), R50.2, U1.18 (B2)
AR_SDAIN2: ARDUINO_NANO1.8 (A4), R48.2; also elsewhere on the board
G2: IO_G2.1, R4.P$2 (2); also elsewhere on the board
G3: IO_G3.1, R5.P$2 (2); also elsewhere on the board
G36: U1.5 (A4); also elsewhere on the board
G37: U1.6 (A5); also elsewhere on the board
GND: ARDUINO_NANO1.14 (GND), ARDUINO_NANO1.19 (GND), C1.2, C2.1, C3.2, C5.2, C6.2, C7.2, C8.2, C9.2, C10.2, C12.2, C13.2, C14.2, C15.2, C16.2, C17.2, C18.2, C19.2, C20.2, C21.2, C22.2, C23.2, C24.2, C25.2, C26.2, C27.2, C28.2, C29.2, C30.2, C31.2, C38.2, C39.2, C40.2, C41.2, C42.2, C43.2, C44.1, C45.1, C46.1, C47.2, IC11.2 (GND), IO_G2.2, IO_G2.3 (2), IO_G2.4 (2), IO_G2.5 (2), IO_G3.2, IO_G3.3 (2), IO_G3.4 (2), IO_G3.5 (2), IO_H4.2, IO_H4.3 (2), IO_H4.4 (2), IO_H4.5 (2), IO_H5.2, IO_H5.3 (2), IO_H5.4 (2), IO_H5.5 (2), J1.6, J1.8, J4.1, J4.2, J4.3, J4.4, PULSESUMOUT.2, PULSESUMOUT.3 (2), PULSESUMOUT.4 (2), PULSESUMOUT.5 (2), R4.P$1 (1), R5.P$1 (1), R15.P$1 (1), R16.P$1 (1), R_VH.1 (A), R_VL.1 (A), U1.11 (GND), U2.1 (GND); also elsewhere on the board
H4: IO_H4.1, R15.P$2 (2); also elsewhere on the board
H5: IO_H5.1, R16.P$2 (2); also elsewhere on the board
IO1: J5.1; also elsewhere on the board
unnamed: PULSESUMOUT.1, R34.2
OFFSETIN1: J5.4; also elsewhere on the board
OFFSETIN2: J5.7; also elsewhere on the board
OP2BUF: J5.8; also elsewhere on the board
OPOUT1_H10: J5.3; also elsewhere on the board
OPOUT2_H11: J5.6; also elsewhere on the board
PULSESUMOUT: J5.2, R34.1; also elsewhere on the board
SCLIN: U1.8 (A7); also elsewhere on the board
SDAIN: U1.3 (A2); also elsewhere on the board
TRANSOUT: J5.5; also elsewhere on the board
VH: C7.1, J1.3, R_VH.2 (S); also elsewhere on the board
VIN: ARDUINO_NANO1.15 (VIN)
VIN+: C39.1, C42.1, J1.5, L1.1
VIN+CLEAN: C38.1, C43.1, IC11.1 (VI), L1.2
VIN-: C40.1, C44.2, J1.7, L2.1
VIN-CLEAN: C41.1, C45.2, L2.2, U2.2 (IN)
VL: C8.1, J1.4, R_VL.2 (S); also elsewhere on the board
VS+: C1.1, C3.1, C6.1, C9.1, C16.1, C18.1, C20.1, C22.1, C24.1, C26.1, C28.1, C30.1, C47.1, IC11.3 (VO), J1.2, J6.1, J6.2, J6.3, J6.4, R_VH.3 (E), U1.19 (VCCB); also elsewhere on the board
VS-: C2.2, C10.1, C15.1, C17.1, C19.1, C21.1, C23.1, C25.1, C27.1, C29.1, C31.1, C46.2, J7.1, J7.2, J7.3, J7.4, R_VL.3 (E), U2.3 (OUT); also elsewhere on the board

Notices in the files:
parts and their libraries:
SparkFun-Connectors: Licensing: Creative Commons ShareAlike 4.0 International - https://creativecommons.org/licenses/by-sa/4.0
